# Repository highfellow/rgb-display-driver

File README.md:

rgb-display-driver
==================

This is a project to make an open hardware display driver for 12v RGB LED strips, with various nice effects including a sound to light mode (colour organ). It is still very much work in progress, so don't expect that it will be usable for any particular purpose at the moment. I've mostly finished designing the electronics and testing them on breadboard, with circuit as shown in the KiCAD schematic. I'm just starting to work on laying out the PCB.

Below are some very rough instructions for compiling the software. I'll put up some better docs soon hopefully.

* The main arduino project is in the `code/` subdirectory.
* The `menu/` subdirectory contains a library which drives the LCD menu system. This needs to be symlinked to the libraries directory of your arduino sketchbook.
* The menu system is currently dependent on the Standard Template Library for Arduino released here: http://andybrown.me.uk/2011/01/15/the-standard-template-library-stl-for-avr-with-c-streams/ . Follow the instructions there to install this. You may need to make the patch described in this comment for it to compile. http://andybrown.me.uk/2011/01/15/the-standard-template-library-stl-for-avr-with-c-streams/#comment-2504271649 . At some point I may well rewrite the library to remove this dependency.

The `pcb/` subdirectory contains a couple of KiCAD projects - one for the main pcb and one for a smaller pcb with the controls attached.

The code files (menu and arduino project) are released under the GPL version 3: http://www.gnu.org/licenses/gpl-3.0.en.html . The KiCAD projects are released under the Creative Commons Attribution-ShareAlike license: http://creativecommons.org/licenses/by-sa/4.0/

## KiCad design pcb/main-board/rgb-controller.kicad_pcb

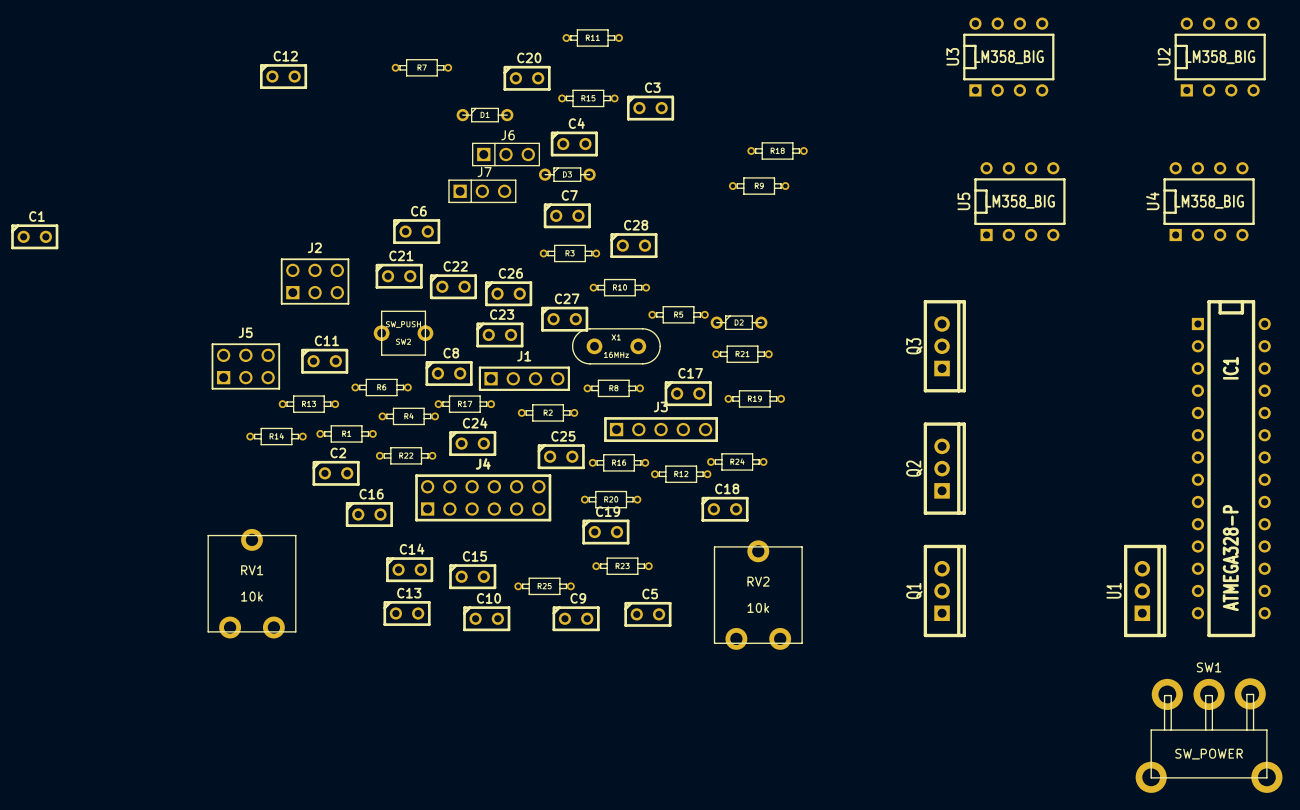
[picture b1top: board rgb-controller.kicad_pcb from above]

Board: 2 copper layers, 77 parts (0 on the bottom side), 55 nets, no tracks yet.

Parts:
C1, C12, C20: 10uF; C1
C2, C3, C4, C5, C8, C9, C10, C11, C14, C15, C18, C19, C26: 100nF; C1
C6, C7: 22pF; C1
C13, C16, C24: 10nF; C1
C17: 47nF; C1
C21, C22, C23, C27, C28: 1uF; C1
C25: 4.7nF; C1
D1, D2, D3: DIODE; D2
IC1: ATMEGA328-P; DIP-28__300
J1: PWR_IN; PIN_ARRAY_4x1
J2: LED_HEADER; pin_array_3x2
J3: UART_HEADER; PIN_ARRAY_5x1
J4: LCD_HEADER; pin_array_6x2
J5: CONTROL_HEADER; pin_array_3x2
J6: AUDIO_HEADER_OUT; PIN_ARRAY_3X1
J7: AUDIO_HEADER_IN; PIN_ARRAY_3X1
Q1, Q2, Q3: STP35NF10; TO220_NUM
R1, R4, R5, R6, R7: 10k; R_MF12
R2, R3: 1M; R_MF12
R8, R22, R25: 33k; R_MF12
R9, R11, R19, R20: 15k; R_MF12
R10, R13: 3.9k; R_MF12
R12, R14: 8.2k; R_MF12
R15, R16, R21, R23: 100k; R_MF12
R17, R18, R24: 6.8k; R_MF12
RV1, RV2: 10k; RV_CB10
SW1: SW_POWER; SW_1101
SW2: SW_PUSH; SW_TACT
U1: 7805_NUM; TO220_NUM
U2, U3, U4, U5: LM358_BIG; DIP-8__300
X1: 16MHz; XTAL_16

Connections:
+5V: C1.1, C2.1, C3.1, IC1.7, IC1.20, J3.2, J4.1, J4.6, J4.11, R1.2, RV1.3, RV2.3, U1.3
+12V: C10.2, C11.2, C19.1, C26.1, J2.4, J2.5, J2.6, R6.1, R15.2, R16.2, R23.2, SW1.2, U1.1, U2.8, U3.8, U4.8, U5.8
/Audio processing/AGND: C12.2, C17.2, C25.2, R2.2, R3.2, R12.1, R14.1, U3.3, U3.6, U3.7
/Audio processing/AUDIO: C13.2, C15.2, R8.2, R9.1, U3.1
/Colour Organ/LEVEL_BLUE: C23.1, D2.2, IC1.25, R22.2
/Colour Organ/LEVEL_GREEN: C28.1, D3.2, IC1.24, R25.2
/Colour Organ/LEVEL_RED: C22.1, D1.2, IC1.23, R21.2
/DB0: IC1.15, J4.7
/DB1: IC1.16, J4.8
/DB2: IC1.17, J4.9
/DB3: IC1.18, J4.10
/ENC_CCW: IC1.12, J5.3
/ENC_CW: IC1.11, J5.2
/G_BLUE: IC1.6, Q3.1
/G_GREEN: IC1.5, Q2.1
/G_RED: IC1.4, Q1.1
/MODE: IC1.13, J5.4
/PARAM: IC1.19, J5.5
/RS: IC1.14, J4.4
GND: C1.2, C2.2, C3.2, C4.2, C6.2, C7.2, C10.1, C11.1, C12.1, C19.2, C22.2, C23.2, C26.2, C28.2, IC1.8, IC1.22, J1.1, J1.2, J3.1, J4.2, J4.5, J4.12, J5.1, J6.1, J7.1, Q1.3, Q2.3, Q3.3, R7.2, R17.1, R18.1, R21.1, R22.1, R24.1, R25.1, RV1.1, RV2.1, SW2.2, U1.2, U2.4, U3.4, U4.4, U5.4
unnamed: IC1.3, J3.4
unnamed: IC1.2, J3.3
unnamed: J4.3, RV2.2
unnamed: J2.1, Q1.2
unnamed: J2.2, Q2.2
unnamed: C5.1, IC1.1, R1.1, SW2.1
unnamed: J2.3, Q3.2
unnamed: C5.2, J3.5
unnamed: J1.3, J1.4, SW1.1
unnamed: C7.1, IC1.10, X1.2
unnamed: C6.1, IC1.9, X1.1
unnamed: C4.1, IC1.21, RV1.2
unnamed: R4.2, R5.2, R8.1, U3.2
unnamed: R5.1, U2.6, U2.7
unnamed: C9.1, J6.2, J7.2
unnamed: C8.1, J6.3, J7.3
unnamed: R4.1, U2.1, U2.2
unnamed: R6.2, R7.1, U3.5
unnamed: C8.2, R2.1, U2.3
unnamed: C9.2, R3.1, U2.5
unnamed: C25.1, R20.2, U5.5
unnamed: C18.1, R14.2, U5.3
unnamed: R13.2, R19.1, U5.1, U5.2
unnamed: C24.2, R19.2, R20.1
unnamed: C27.1, D3.1, R23.1, R24.2
unnamed: C16.1, R12.2, U4.5
unnamed: C15.1, C18.2, R13.1
unnamed: C14.1, C20.2, U4.1, U4.2
unnamed: C21.2, R10.2, U4.6, U4.7
unnamed: C24.1, C27.2, U5.6, U5.7
unnamed: C13.1, C16.2, R10.1
unnamed: C20.1, D1.1, R15.1, R17.2
unnamed: C21.1, D2.1, R16.1, R18.2
unnamed: C17.1, R11.2, U4.3
unnamed: C14.2, R9.2, R11.1

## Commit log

2012-10-12 initial version
2012-10-13 working again
2012-10-30 added mode cycling switch
2012-10-31 Hue sat colour cycling
2012-10-31 with speed control on colour cycling
2012-10-31 gitignore change
2012-11-01 README change
2012-11-02 int maths working in RGB mode
2012-11-02 int maths working with hsv colours
2012-11-02 int maths + first 3 modes
2012-11-02 changed timings
2014-04-30 loads of changes; now working with LCD menu system
2016-04-26 moved code into subdirectory
2016-04-26 added directory with pcb files.
2016-04-26 added menu system and README.md
2016-05-08 moved strings to flash memory
2016-10-22 working on finding components for parts
2016-10-23 finished choosing components for main board
2016-10-23 found components for controls board
2018-10-16 misc. changes
